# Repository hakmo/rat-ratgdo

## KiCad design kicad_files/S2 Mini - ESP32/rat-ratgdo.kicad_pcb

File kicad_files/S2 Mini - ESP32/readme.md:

## Overview
This is a rat-ratgdo carrier board for a [Wemos S2 mini](https://www.wemos.cc/en/latest/s2/s2_mini.html). In addition to standard ratgdo functionality, it breaks out 2 I2C buses (one with a Qwiic/Stemma compatible connector) as well as a UART for use with other sensors.

_Assembled board with S2 mini and BME280 module mounted_

[Get boards from OSHPark](https://oshpark.com/shared_projects/v4UJMWZY)

[ESPHome YAML](garage-door.yaml)

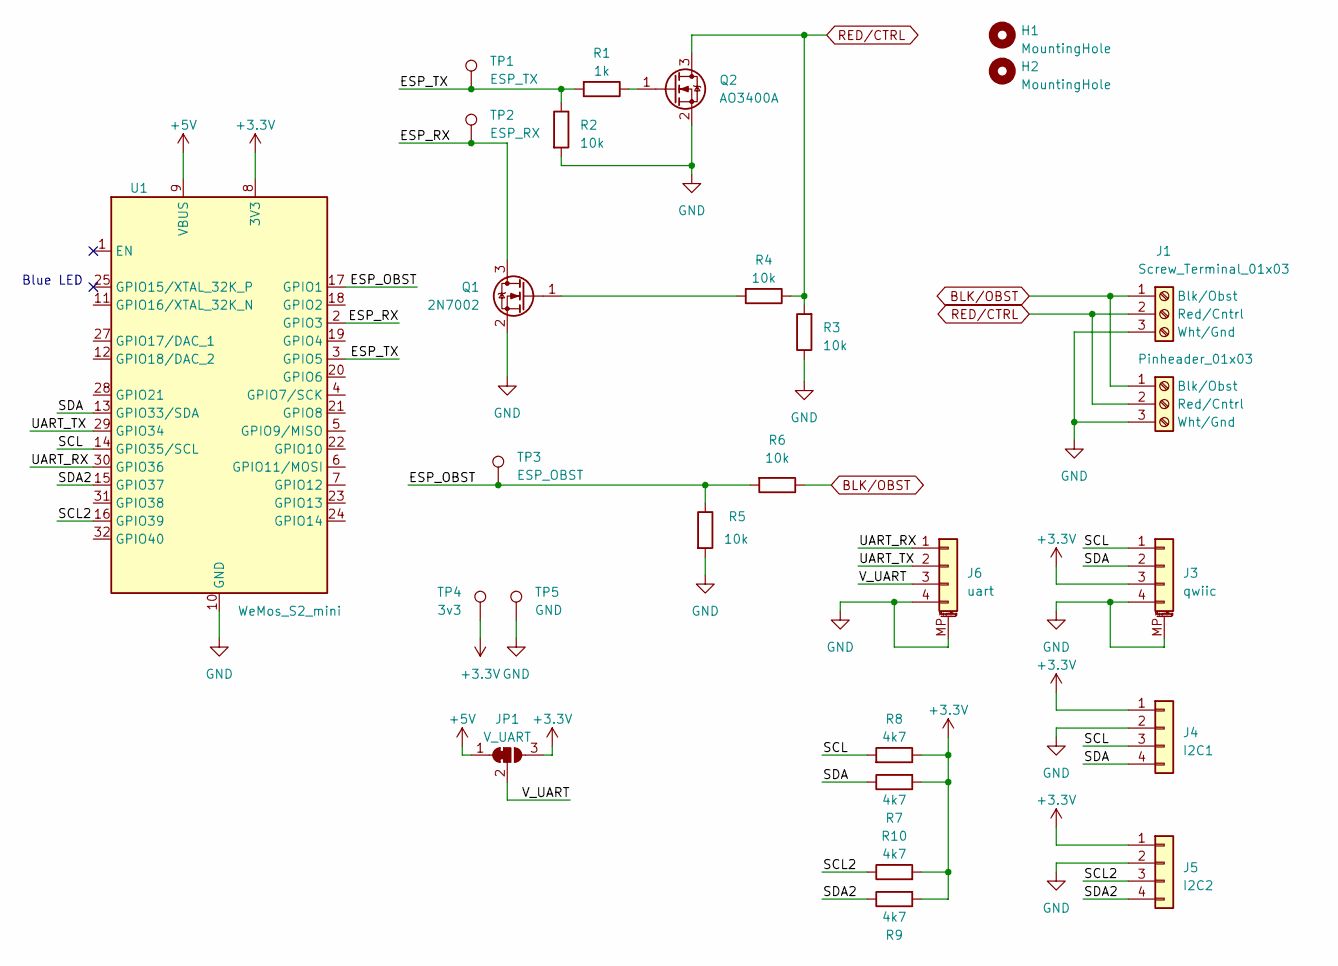
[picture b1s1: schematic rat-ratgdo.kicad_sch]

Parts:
H1, H2: MountingHole; MountingHole_3.2mm_M3
J1: Screw_Terminal_01x03; TerminalBlock_Phoenix_MKDS-1,5-3_1x03_P5.00mm_Horizontal
J2: Pinheader_01x03; PinHeader_1x03_P2.54mm_Vertical
J3: qwiic; JST_SH_BM04B-SRSS-TB_1x04-1MP_P1.00mm_Vertical
J4: I2C1; PinHeader_1x04_P2.54mm_Vertical
J5: I2C2; PinHeader_1x04_P2.54mm_Vertical
J6: uart; JST_SH_BM04B-SRSS-TB_1x04-1MP_P1.00mm_Vertical
JP1: V_UART; SolderJumper-3_P1.3mm_Bridged12_RoundedPad1.0x1.5mm_NumberL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
Q1: 2N7002; SOT-23_Handsoldering
Q2: AO3400A; SOT-23_Handsoldering
R1: 1k; R_0805_2012Metric_Pad1.20x1.40mm_HandSolder
R2, R3, R4, R5, R6: 10k; R_0805_2012Metric_Pad1.20x1.40mm_HandSolder
R7, R8, R9, R10: 4k7; R_0805_2012Metric_Pad1.20x1.40mm_HandSolder
TP1: ESP_TX; TestPoint_Pad_D1.5mm
TP2: ESP_RX; TestPoint_Pad_D1.5mm
TP3: ESP_OBST; TestPoint_Pad_D1.5mm
TP4: 3v3; TestPoint_Pad_D1.5mm
TP5: GND; TestPoint_Pad_D1.5mm
U1: WeMos_S2_mini; WEMOS_S2_mini

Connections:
+3.3V: J3.3, J4.1, J5.1, JP1.3 (B), R7.2, R8.1, R9.2, R10.2, TP4.1, U1.8 (3V3)
+5V: JP1.1 (A), U1.9 (VBUS)
/ESP_OBST: R5.1, R6.2, TP3.1, U1.17 (GPIO1)
/ESP_RX: Q1.3 (D), TP2.1, U1.2 (GPIO3)
/ESP_TX: R1.2, R2.1, TP1.1, U1.3 (GPIO5)
/SCL: J3.1, J4.3, R8.2, U1.14 (GPIO35/SCL)
/SCL2: J5.3, R10.1, U1.16 (GPIO39)
/SDA: J3.2, J4.4, R7.1, U1.13 (GPIO33/SDA)
/SDA2: J5.4, R9.1, U1.15 (GPIO37)
/UART_RX: J6.1, U1.30 (GPIO36)
/UART_TX: J6.2, U1.29 (GPIO34)
/V_UART: J6.3, JP1.2 (C)
BLK/OBST: J1.1 (Blk/Obst), J2.1 (Blk/Obst), R6.1
GND: J1.3 (Wht/Gnd), J2.3 (Wht/Gnd), J3.4, J3.MP (MountPin), J4.2, J5.2, J6.4, J6.MP (MountPin), Q1.2 (S), Q2.2 (S), R2.2, R3.1, R5.2, TP5.1, U1.10 (GND), U1.26 (GND)
unnamed: Q1.1 (G), R4.2
unnamed: Q2.1 (G), R1.1
RED/CTRL: J1.2 (Red/Cntrl), J2.2 (Red/Cntrl), Q2.3 (D), R3.2, R4.1

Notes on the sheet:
Blue LED

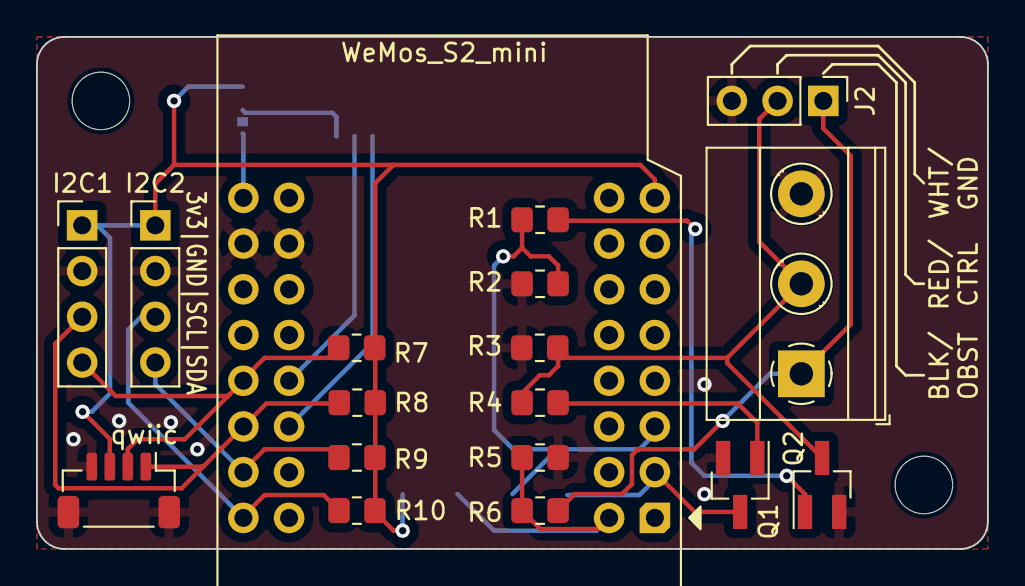
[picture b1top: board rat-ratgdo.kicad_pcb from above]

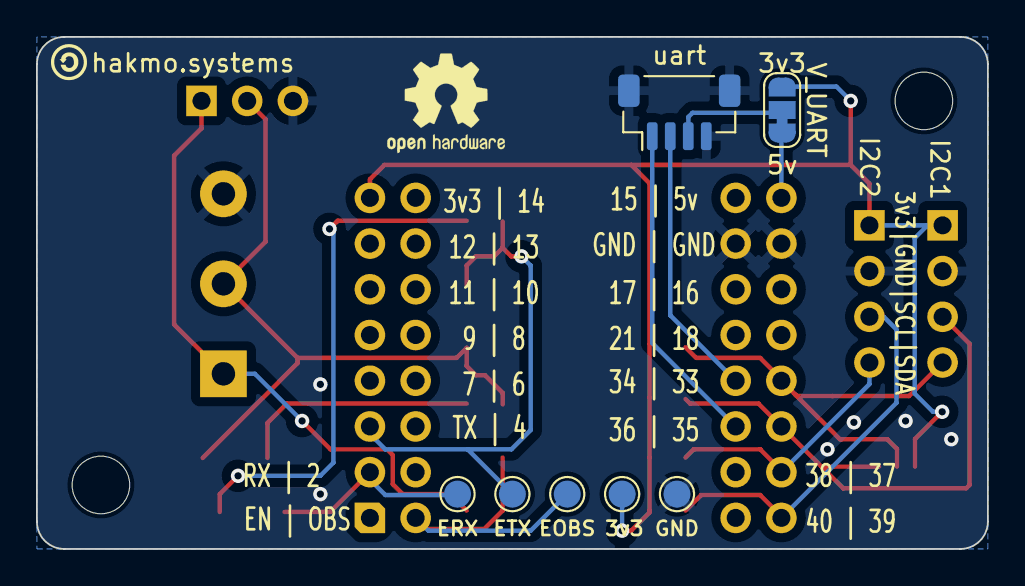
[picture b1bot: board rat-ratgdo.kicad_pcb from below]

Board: 2 copper layers, 52.8 x 28.4 mm, 27 parts (7 on the bottom side), 17 nets.

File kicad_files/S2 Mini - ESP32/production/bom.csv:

Designator,Footprint,Quantity,Value,LCSC Part #
"H1, H2",MountingHole_3.2mm_M3,2,MountingHole,
J1,"TerminalBlock_Phoenix_MKDS-1,5-3_1x03_P5.00mm_Horizontal",1,Screw_Terminal_01x03,
J2,PinHeader_1x03_P2.54mm_Vertical,1,Pinheader_01x03,
J3,JST_SH_BM04B-SRSS-TB_1x04-1MP_P1.00mm_Vertical,1,qwiic,
J4,PinHeader_1x04_P2.54mm_Vertical,1,I2C1,
J5,PinHeader_1x04_P2.54mm_Vertical,1,I2C2,
J6,JST_SH_BM04B-SRSS-TB_1x04-1MP_P1.00mm_Vertical,1,uart,
JP1,SolderJumper-3_P1.3mm_Bridged12_RoundedPad1.0x1.5mm_NumberLabels,1,V_UART,
Q1,SOT-23_Handsoldering,1,2N7002,
Q2,SOT-23_Handsoldering,1,AO3400A,
R1,0805,1,1k,
"R10, R7, R8, R9",0805,4,4k7,
"R2, R3, R4, R5, R6",0805,5,10k,
TP1,TestPoint_Pad_D1.5mm,1,ETX,
TP2,TestPoint_Pad_D1.5mm,1,ERX,
TP3,TestPoint_Pad_D1.5mm,1,EOBS,
TP4,TestPoint_Pad_D1.5mm,1,3v3,
TP5,TestPoint_Pad_D1.5mm,1,GND,
U1,WEMOS_S2_mini,1,WeMos_S2_mini,

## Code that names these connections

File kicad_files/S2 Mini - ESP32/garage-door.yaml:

substitutions:
  id_prefix: ratgdov2
  friendly_name: "RATGDOv2"
  uart_tx_pin: GPIO5
  uart_rx_pin: GPIO3
  input_obst_pin: GPIO1
  status_door_pin: "6"
  status_obstruction_pin: "12"
  dry_contact_open_pin: "7"
  dry_contact_close_pin: "9"
  dry_contact_light_pin: "18"

web_server:

esphome:
  name: garage-door
  friendly_name: garage-door
  #name_add_mac_suffix: true
  project:
    name: ratgdo.esphome
    version: "2.0"

esp32:
  board: lolin_s2_mini

# I2C
i2c:
  # I2C1 / QWIIC
  - id: i2c_1
    sda: GPIO33
    scl: GPIO35
    scan: False
  # I2C2
  - id: i2c_2
    sda: GPIO37
    scl: GPIO39
    scan: False
    
# UART
uart:
  tx_pin: GPIO34
  rx_pin: GPIO36
  baud_rate: 115200

sensor:
  - platform: bme280_i2c
    i2c_id: i2c_2
    address: 0x76
    update_interval: 10min
    iir_filter: 16x
    temperature:
      name: "Garage Temperature"
      oversampling: 16x
      id: garage_temperature
    pressure:
      name: "Garage Pressure"
      id: garage_pressure
    humidity:
      name: "Garage Humidity"
      id: garage_humidity
  - platform: template
    name: "Garage Absolute Humidity"
    update_interval: 10min
    lambda: |-
      const float mw = 18.01534;    // molar mass of water g/mol
      const float r = 8.31447215;   // Universal gas constant J/mol/K
      return (6.112 * powf(2.718281828, (17.67 * id(garage_temperature).state) /
        (id(garage_temperature).state + 243.5)) * id(garage_humidity).state * mw) /
        ((273.15 + id(garage_temperature).state) * r); // in grams/m^3
    accuracy_decimals: 2
    unit_of_measurement: "g/m³"
    icon: "mdi:water"
#  - platform: internal_temperature
#    name: "Garage Door Controller Temperature"


dashboard_import:
  package_import_url: github://ratgdo/esphome-ratgdo/v2board_esp32_lolin_s2_mini.yaml@main

packages:
  remote_package:
    url: https://github.com/ratgdo/esphome-ratgdo
    files: [base.yaml]
    refresh: 1s

# Sync time with Home Assistant.
time:
  - platform: homeassistant
    id: homeassistant_time

# Enable Home Assistant API
api:
  encryption:
    key: ""

ota:
  platform: esphome
  password: ""

improv_serial:

wifi:
  ssid: !secret wifi_ssid
  password: !secret wifi_password

  # Enable fallback hotspot (captive portal) in case wifi connection fails
  ap:
    ssid: "Garage-Door Fallback Hotspot"
    password: ""

captive_portal:

logger:

# Use S2 mini onboard LED to signal wifi connectivity
# https://community.home-assistant.io/t/esphome-esp32-wifi-connected-led/184399/9
# binary_sensor:
#   - platform: template
#     name: Wifi Connection
#     id: wifi_connected
#     lambda: return(wifi.connected);
#     on_press:
#       then:
#         - light.turn_on:
#             id: led
#             effect: none
#     on_release:
#       then:
#         - light.turn_on:
#             id: led
#             effect: Pulse

# output:
#   - platform: ledc
#     id: blue_led
#     pin: GPIO15
#     inverted: True

# light:
#   - platform: monochromatic
#     name: Blue LED
#     id: led
#     output: blue_led
#     internal: true
#     effects:
#       - pulse:

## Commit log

2024-11-05 Add Wemos S2 mini based PCB
2024-11-05 Update readme links
